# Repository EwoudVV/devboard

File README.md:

# Devboard

A small STM32 devboard for deving

## details
- Compatible with a breadboard
- USB-C programming port
- SD card holder
- 32 header pins total: 22 GPIO, including 9 analog inputs, plus debug and power pins
- STM32 MCU
- 4 layer board
- 24x44mm board size
- 2 side component assembly

## images
The board in PCB editor: 
The board in 3d viewer: 

## goal
- Purpose: a functional and useful devboard
- MCU: STM32 (MCU_ST_STM32F4:STM32F411CEUx)
- Features: USB-C + UART, SD card, expanded GPIO
- Size: as small as possible

## status

project finished!!
Once I get funding, I will order 10 assembled PCBs from PCBway.

## bom

Parts from the [PCBWay BOM](production/pcbway_bom.xlsx), with quantities for one board. The [KiCad CSV export](production/bom.csv) is also available.

| Reference | Qty | Manufacturer | Part number | Package |
| --- | ---: | --- | --- | --- |
| C1, C2 | 2 | Murata | GRM1555C1H180JA01D | 0402 |
| C3, C6, C7, C8, C9, C11, C15 | 7 | Samsung | CL05B104KB5NNNC | 0402 |
| C5, C13 | 2 | Samsung | CL05A105KO5NNNC | 0402 |
| C4, C14 | 2 | Samsung | CL05A106KP5NNNC | 0402 |
| C10 | 1 | Murata | GRM155R61A475MEAA | 0402 |
| C12 | 1 | Murata | GRM155R61A225KE95D | 0402 |
| R3, R4 | 2 | Yageo | RC0402FR-075K1L | 0402 |
| R9, R10, R11, R12, R13 | 5 | Yageo | RC0402FR-0747KL | 0402 |
| R8 | 1 | Yageo | RC0402FR-0710RL | 0402 |
| R1, R2, R6 | 3 | Yageo | RC0402FR-0710KL | 0402 |
| R5 | 1 | Yageo | RC0402FR-071KL | 0402 |
| U1 | 1 | STMicroelectronics | STM32F411CEU6 | QFN-48 7x7 |
| U2 | 1 | Diodes Incorporated | AP2112K-3.3TRG1 | SOT-23-5 |
| D1 | 1 | STMicroelectronics | USBLC6-2SC6 | SOT-23-6 |
| LED1 | 1 | Lite-On | LTST-C190GKT | 0603 |
| Y1 | 1 | Abracon | ABM3-25.000MHZ-D2Y-T | 5.0x3.2mm |
| J1 | 1 | GCT | USB4105-GF-A | USB-C 16P |
| J2 | 1 | Hirose | DM3AT-SF-PEJM5 | microSD |
| SW1, SW2, SW3 | 3 | C&K | PTS645SM43SMTR92 LFS | 6x6mm SMD |

The four through-hole headers are soldered separately and are not included in this BOM. For J1, check the USB4105 pin-length variant against the footprint, as noted in the PCBWay BOM.

## repo structure
- `devboard.kicad_pro` / `.kicad_sch` / `.kicad_pcb`: KiCad project (root)
- `journal.md`: devlog journals
- `README.md`: this file
- `production`: production files, like gerbers, bom, cpl
- `docs/pinout.md`: header pinout and on-board connections
- `firmware`: starter LED, button, and USB serial firmware

## getting started

[Pinout and connections](docs/pinout.md)

[Building and flashing the starter firmware](firmware/README.md)

Designed by EVV
Made for Hack Club Half Life
9/16/26

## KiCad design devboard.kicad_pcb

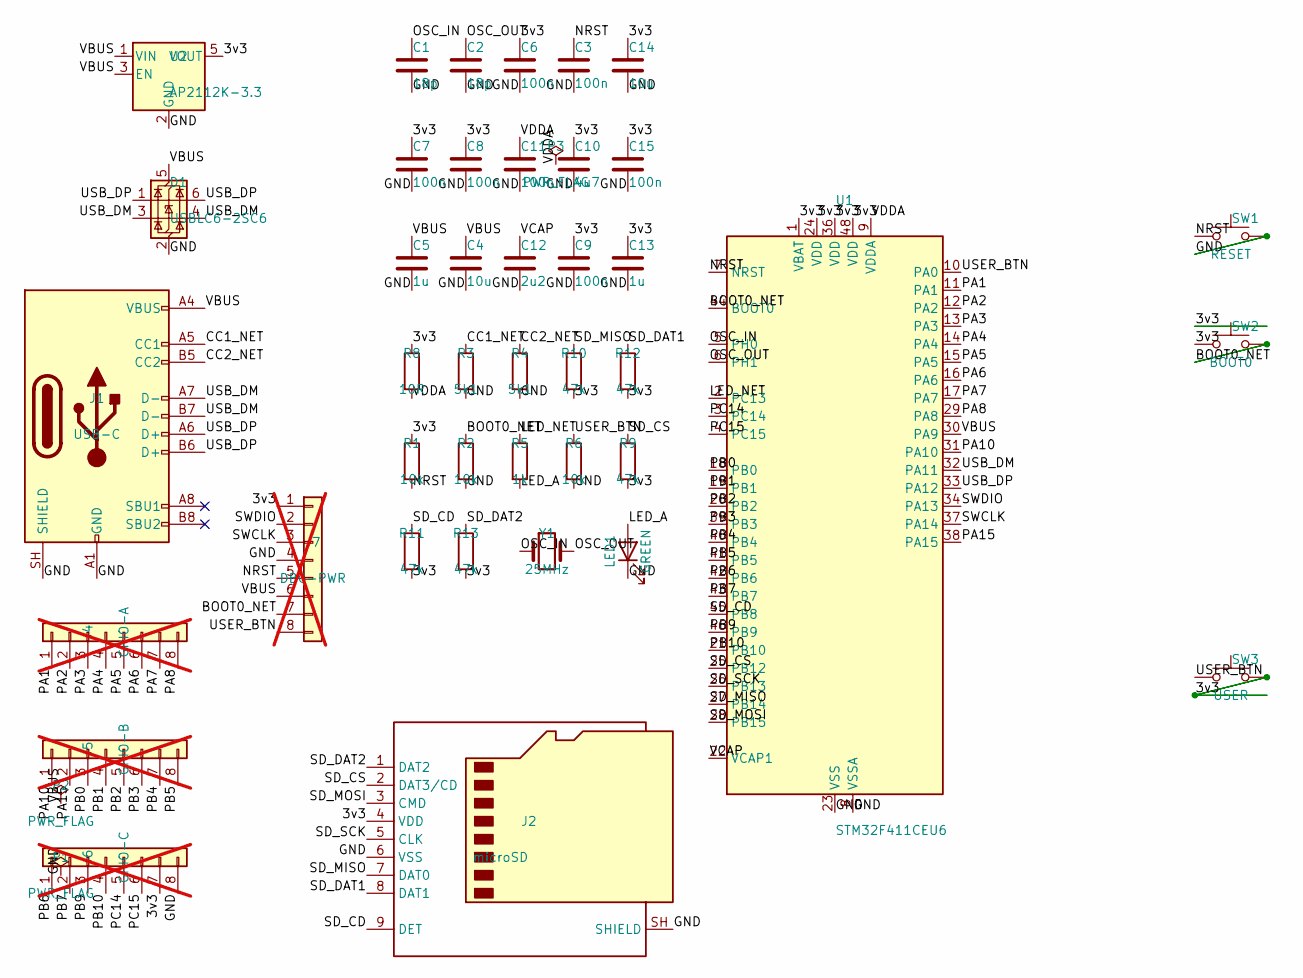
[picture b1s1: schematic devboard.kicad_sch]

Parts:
C1, C2: 18p; C_0402_1005Metric
C3, C6, C7, C8, C9, C11, C15: 100n; C_0402_1005Metric
C4, C14: 10u; C_0402_1005Metric
C5, C13: 1u; C_0402_1005Metric
C10: 4u7; C_0402_1005Metric
C12: 2u2; C_0402_1005Metric
D1: USBLC6-2SC6; SOT-23-6
J1: USB-C; USB_C_Receptacle_GCT_USB4105-xx-A_16P_TopMnt_Horizontal
J2: microSD; microSD_HC_Hirose_DM3AT-SF-PEJM5
J4: GPIO-A; PinHeader_1x08_P2.54mm_Vertical; not fitted
J5: GPIO-B; PinHeader_1x08_P2.54mm_Vertical; not fitted
J6: GPIO-C; PinHeader_1x08_P2.54mm_Vertical; not fitted
J7: DBG-PWR; PinHeader_1x08_P2.54mm_Vertical; not fitted
LED1: GREEN; LED_0603_1608Metric
P1, P2, P3: PWR_FLAG
R1, R2, R6: 10k; R_0402_1005Metric
R3, R4: 5k1; R_0402_1005Metric
R5: 1k; R_0402_1005Metric
R8: 10R; R_0402_1005Metric
R9, R10, R11, R12, R13: 47k; R_0402_1005Metric
SW1: RESET; SW_SPST_PTS645Sx43SMTR92
SW2: BOOT0; SW_SPST_PTS645Sx43SMTR92
SW3: USER; SW_SPST_PTS645Sx43SMTR92
U1: STM32F411CEU6; QFN-48-1EP_7x7mm_P0.5mm_EP5.15x5.15mm
U2: AP2112K-3.3; SOT-23-5
Y1: 25MHz; Crystal_SMD_Abracon_ABM3-2Pin_5.0x3.2mm

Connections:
3v3: C6.1, C7.1, C8.1, C9.1, C10.1, C13.1, C14.1, C15.1, J2.4 (VDD), J6.7, J7.1, R1.1, R8.1, R9.2, R10.2, R11.2, R12.2, R13.2, SW2.1, SW3.2, U1.1 (VBAT), U1.24 (VDD), U1.36 (VDD), U1.48 (VDD), U2.5 (VOUT)
BOOT0_NET: J7.7, R2.1, SW2.2, U1.44 (BOOT0)
CC1_NET: J1.A5 (CC1), R3.1
CC2_NET: J1.B5 (CC2), R4.1
GND: C1.2, C2.2, C3.2, C4.2, C5.2, C6.2, C7.2, C8.2, C9.2, C10.2, C11.2, C12.2, C13.2, C14.2, C15.2, D1.2 (GND), J1.A1 (GND), J1.A12 (GND), J1.B1 (GND), J1.B12 (GND), J1.SH (SHIELD), J2.6 (VSS), J2.SH (SHIELD), J6.8, J7.4, LED1.1 (K), P1.1, R2.2, R3.2, R4.2, R6.2, SW1.2, U1.8 (VSSA), U1.23 (VSS), U1.35 (VSS), U1.47 (VSS), U1.49 (VSS), U2.2 (GND)
LED_A: LED1.2 (A), R5.2
LED_NET: R5.1, U1.2 (PC13)
NRST: C3.1, J7.5, R1.2, SW1.1, U1.7 (NRST)
OSC_IN: C1.1, U1.5 (PH0), Y1.1
OSC_OUT: C2.1, U1.6 (PH1), Y1.2
PA1: J4.1, U1.11 (PA1)
PA2: J4.2, U1.12 (PA2)
PA3: J4.3, U1.13 (PA3)
PA4: J4.4, U1.14 (PA4)
PA5: J4.5, U1.15 (PA5)
PA6: J4.6, U1.16 (PA6)
PA7: J4.7, U1.17 (PA7)
PA8: J4.8, U1.29 (PA8)
PA10: J5.1, U1.31 (PA10)
PA15: J5.2, U1.38 (PA15)
PB0: J5.3, U1.18 (PB0)
PB1: J5.4, U1.19 (PB1)
PB2: J5.5, U1.20 (PB2)
PB3: J5.6, U1.39 (PB3)
PB4: J5.7, U1.40 (PB4)
PB5: J5.8, U1.41 (PB5)
PB6: J6.1, U1.42 (PB6)
PB7: J6.2, U1.43 (PB7)
PB9: J6.3, U1.46 (PB9)
PB10: J6.4, U1.21 (PB10)
PC14: J6.5, U1.3 (PC14)
PC15: J6.6, U1.4 (PC15)
SD_CD: J2.9 (DET), R11.1, U1.45 (PB8)
SD_CS: J2.2 (DAT3/CD), R9.1, U1.25 (PB12)
SD_DAT1: J2.8 (DAT1), R12.1
SD_DAT2: J2.1 (DAT2), R13.1
SD_MISO: J2.7 (DAT0), R10.1, U1.27 (PB14)
SD_MOSI: J2.3 (CMD), U1.28 (PB15)
SD_SCK: J2.5 (CLK), U1.26 (PB13)
SWCLK: J7.3, U1.37 (PA14)
SWDIO: J7.2, U1.34 (PA13)
USB_DM: D1.3 (I/O2), D1.4 (I/O2), J1.A7 (D-), J1.B7 (D-), U1.32 (PA11)
USB_DP: D1.1 (I/O1), D1.6 (I/O1), J1.A6 (D+), J1.B6 (D+), U1.33 (PA12)
USER_BTN: J7.8, R6.1, SW3.1, U1.10 (PA0)
VBUS: C4.1, C5.1, D1.5 (VBUS), J1.A4 (VBUS), J1.A9 (VBUS), J1.B4 (VBUS), J1.B9 (VBUS), J7.6, P2.1, U1.30 (PA9), U2.1 (VIN), U2.3 (EN)
VCAP: C12.1, U1.22 (VCAP1)
VDDA: C11.1, P3.1, R8.2, U1.9 (VDDA)

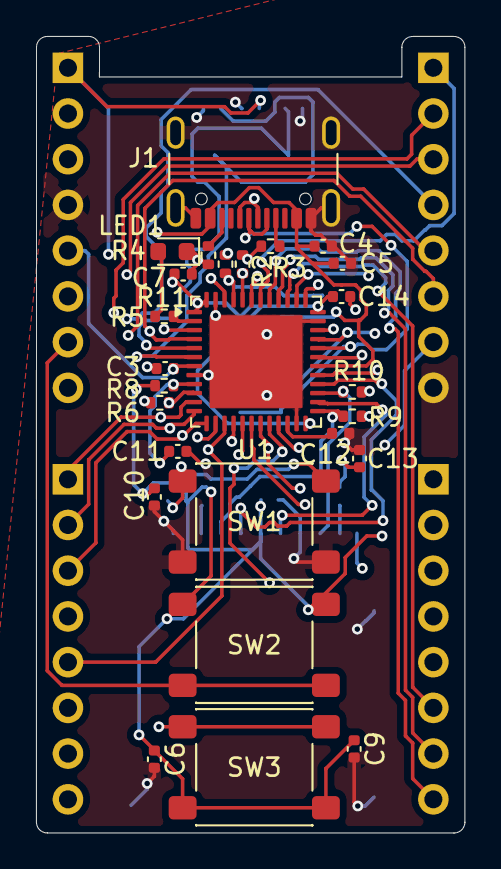
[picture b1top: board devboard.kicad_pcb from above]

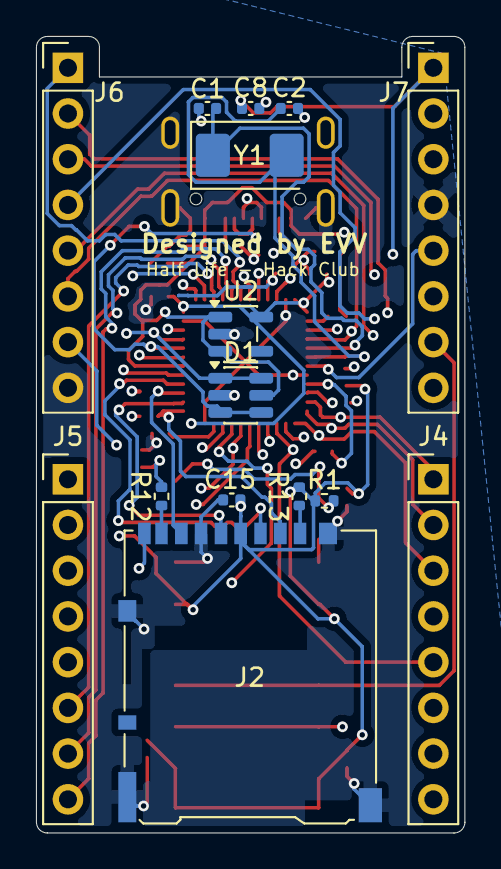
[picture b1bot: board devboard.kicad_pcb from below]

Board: 4 copper layers, 23.8 x 44.3 mm, 41 parts (15 on the bottom side), 47 nets.

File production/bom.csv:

"Refs","Value","Footprint","Qty","DNP"
"C1","18p","Capacitor_SMD:C_0402_1005Metric","1",""
"C2","18p","Capacitor_SMD:C_0402_1005Metric","1",""
"C3","100n","Capacitor_SMD:C_0402_1005Metric","1",""
"C4","10u","Capacitor_SMD:C_0402_1005Metric","1",""
"C5","1u","Capacitor_SMD:C_0402_1005Metric","1",""
"C6","100n","Capacitor_SMD:C_0402_1005Metric","1",""
"C7","100n","Capacitor_SMD:C_0402_1005Metric","1",""
"C8","100n","Capacitor_SMD:C_0402_1005Metric","1",""
"C9","100n","Capacitor_SMD:C_0402_1005Metric","1",""
"C10","4u7","Capacitor_SMD:C_0402_1005Metric","1",""
"C11","100n","Capacitor_SMD:C_0402_1005Metric","1",""
"C12","2u2","Capacitor_SMD:C_0402_1005Metric","1",""
"C13","1u","Capacitor_SMD:C_0402_1005Metric","1",""
"C14","10u","Capacitor_SMD:C_0402_1005Metric","1",""
"C15","100n","Capacitor_SMD:C_0402_1005Metric","1",""
"D1","USBLC6-2SC6","Package_TO_SOT_SMD:SOT-23-6","1",""
"J1","USB-C","Connector_USB:USB_C_Receptacle_GCT_USB4105-xx-A_16P_TopMnt_Horizontal","1",""
"J2","microSD","Connector_Card:microSD_HC_Hirose_DM3AT-SF-PEJM5","1",""
"LED1","GREEN","LED_SMD:LED_0603_1608Metric","1",""
"P1","PWR_FLAG","","1",""
"P2","PWR_FLAG","","1",""
"P3","PWR_FLAG","","1",""
"R1","10k","Resistor_SMD:R_0402_1005Metric","1",""
"R2","10k","Resistor_SMD:R_0402_1005Metric","1",""
"R3","5k1","Resistor_SMD:R_0402_1005Metric","1",""
"R4","5k1","Resistor_SMD:R_0402_1005Metric","1",""
"R5","1k","Resistor_SMD:R_0402_1005Metric","1",""
"R6","10k","Resistor_SMD:R_0402_1005Metric","1",""
"R8","10R","Resistor_SMD:R_0402_1005Metric","1",""
"R9","47k","Resistor_SMD:R_0402_1005Metric","1",""
"R10","47k","Resistor_SMD:R_0402_1005Metric","1",""
"R11","47k","Resistor_SMD:R_0402_1005Metric","1",""
"R12","47k","Resistor_SMD:R_0402_1005Metric","1",""
"R13","47k","Resistor_SMD:R_0402_1005Metric","1",""
"SW1","RESET","Button_Switch_SMD:SW_SPST_PTS645Sx43SMTR92","1",""
"SW2","BOOT0","Button_Switch_SMD:SW_SPST_PTS645Sx43SMTR92","1",""
"SW3","USER","Button_Switch_SMD:SW_SPST_PTS645Sx43SMTR92","1",""
"U1","STM32F411CEU6","Package_DFN_QFN:QFN-48-1EP_7x7mm_P0.5mm_EP5.15x5.15mm","1",""
"U2","AP2112K-3.3","Package_TO_SOT_SMD:SOT-23-5","1",""
"Y1","25MHz","Crystal:Crystal_SMD_Abracon_ABM3-2Pin_5.0x3.2mm","1",""
